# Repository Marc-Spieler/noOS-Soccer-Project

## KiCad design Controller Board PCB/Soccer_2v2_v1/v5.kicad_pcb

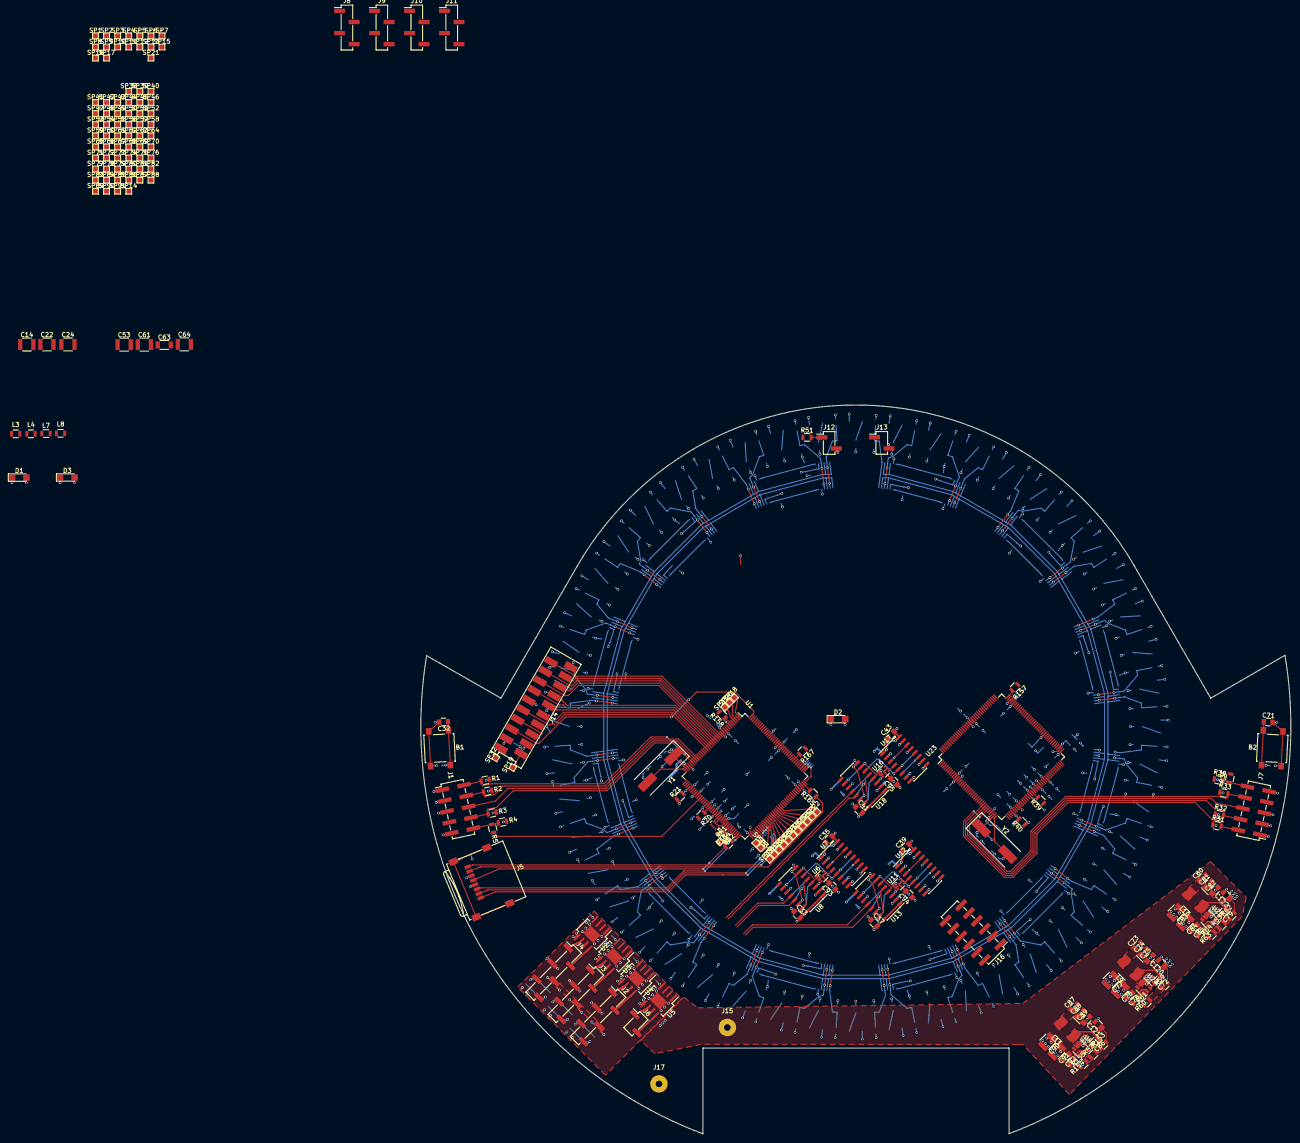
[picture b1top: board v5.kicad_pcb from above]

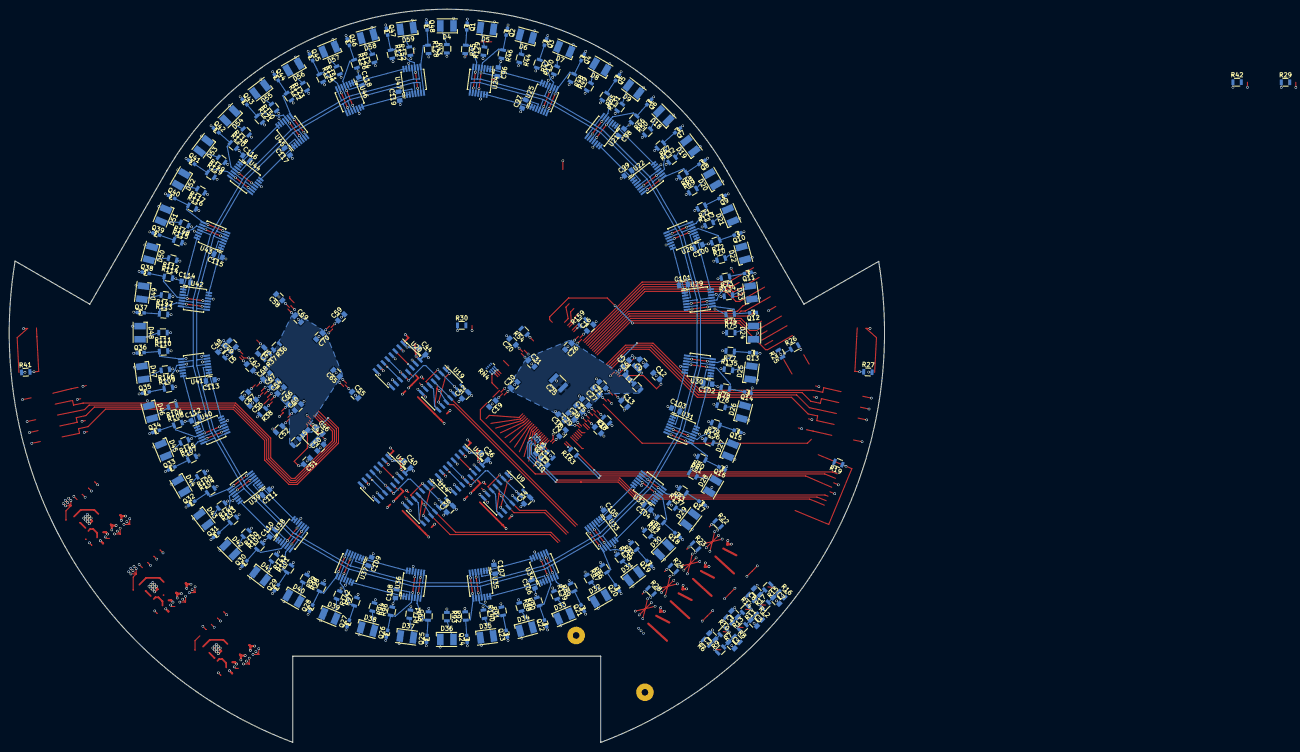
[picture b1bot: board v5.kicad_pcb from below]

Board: 4 copper layers, 199.2 x 166.8 mm, 554 parts (339 on the bottom side), 422 nets.

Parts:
B1, B2: BUTTON; SW_SPST_B3S-1000
C1, C2, C3, C4, C7, C8: opt.; C_0805
C5, C10, C11, C15, C16, C17, C18, C19, C20, C21, C23, C26, C27, C28, C29, C30, C31, C33, C34, C35, C36, C37, C38, C39, C40, C41, C42, C43, C44, C46, C48, C49, C54, C55, C56, C57, C58, C59, C60, C62, C65, C66, C67, C68, C69, C70, C72, C78, C79, C85, C86, C92, C93, C94, C95, C96, C97, C98, C99, C100, C101, C102, C103, C104, C105, C106, C107, C108, C109, C110, C111, C112, C113, C114, C115, C116, C117, C118, C119: 100n; C_0805
C6, C14, C22, C24, C25, C47, C53, C61, C64, C76, C77, C83, C84, C90, C91: 10u; C_1210
C9, C12, C13, C50, C51, C52: 22p; C_0805
C32, C71: 1u; C_0805
C45: 10n; C_0805
C63: 10u; C_1206
C73, C74, C75, C80, C81, C82, C87, C88, C89, C120, C121, C122: 22u; C_0805
D1: POW B; LED_1206
D2: LED O; LED_1206
D3: LED G; LED_1206
D4, D5, D6, D7, D8, D9, D18, D19, D20, D21, D22, D23, D24, D25, D26, D27, D28, D29, D30, D31, D32, D33, D34, D35, D36, D37, D38, D39, D40, D41, D42, D43, D44, D45, D46, D47, D48, D49, D50, D51, D52, D53, D54, D55, D56, D57, D58, D59: VLMW41R1T1; LED_PLCC-2
J1, J7: JTAG; Pin_Header_Straight_2x05_Pitch2.54mm_SMD
J2: Motor + Enc 1; Pin_Header_Straight_1x06_Pitch2.54mm_SMD_Pin1Left
J3: Motor + Enc 2; Pin_Header_Straight_1x06_Pitch2.54mm_SMD_Pin1Left
J4: Motor + Enc 3; Pin_Header_Straight_1x06_Pitch2.54mm_SMD_Pin1Left
J5: Micro_SD_Card; microSD_Card_Receptacle_Wuerth_693072010801
J6: Motor 4; Pin_Header_Straight_1x02_Pitch2.54mm_SMD_Pin1Left
J8: Ultrasonic 1; Pin_Header_Straight_1x04_Pitch2.54mm_SMD_Pin1Left
J9: Ultrasonic 2; Pin_Header_Straight_1x04_Pitch2.54mm_SMD_Pin1Left
J10: Ultrasonic 3; Pin_Header_Straight_1x04_Pitch2.54mm_SMD_Pin1Left
J11: Ultrasonic 4; Pin_Header_Straight_1x04_Pitch2.54mm_SMD_Pin1Left
J12: light_barrier transmitter; Pin_Header_Straight_1x02_Pitch2.54mm_SMD_Pin1Left
J13: light_barrier reciver; Pin_Header_Straight_1x02_Pitch2.54mm_SMD_Pin1Left
J14: UI+top; 2178711_Wire-To-Board_20-Pin_1,27mm_SMD
J15: POW_12V; SolderWirePad_single_1-5mmDrill
J16: Raspberry Pi; Pin_Header_Straight_2x06_Pitch2.54mm_SMD
J17: POW_GND; SolderWirePad_single_1-5mmDrill
L1, L2, L3, L4, L5, L6, L7, L8: 74279206; L_0805
L9, L10, L11: SRP5015TA-3R3M
Q1, Q2, Q3, Q4, Q5, Q6, Q7, Q8, Q9, Q10, Q11, Q12, Q13, Q14, Q15, Q16, Q17, Q18, Q19, Q20, Q21, Q22, Q23, Q24, Q25, Q26, Q27, Q28, Q29, Q30, Q31, Q32, Q33, Q34, Q35, Q36, Q37, Q38, Q39, Q40, Q41, Q42, Q43, Q44, Q45, Q46, Q47, Q48: KDT00030TR; ChipLED
R1, R2, R3, R4, R20, R31, R32, R33, R34, R37, R39: 100K; R_0805
R5, R18, R35, R38: 0; R_0805
R6, R8, R10, R12, R14, R16: 3.3K; R_0805
R7, R9, R11, R13, R15, R17: 2.2K; R_0805
R19: opt.; R_0805
R21, R40: 6.8K; R_0805
R22, R23, R24, R28: 27K; R_0805
R25, R26: 1.8K; R_0805
R27, R30, R41, R42: 68; R_0805
R29: 82; R_0805
R36: 330K; R_0805
R43, R44, R49, R50, R51, R69, R70, R75, R76, R81, R82, R87, R88, R93, R94, R99, R100, R105, R106, R111, R112, R117, R118, R123, R124, R129, R130, R131, R132, R133, R134, R135, R136, R137, R138, R139, R140, R141, R142, R143, R144, R145, R146, R147, R148, R149, R150, R151, R152: 160; R_0805
R45, R46, R47, R48, R65, R66, R67, R68, R71, R72, R73, R74, R77, R78, R79, R80, R83, R84, R85, R86, R89, R90, R91, R92, R95, R96, R97, R98, R101, R102, R103, R104, R107, R108, R109, R110, R113, R114, R115, R116, R119, R120, R121, R122, R125, R126, R127, R128: 6.2K; R_0805
R52, R53: 3.9K; R_0805
R54, R157, R158, R159, R163, R164, R165, R167: 22; R_0805
R59: 33.2K; R_0805
R60, R61, R63, R64, R154, R155: 10K; R_0805
R62, R153: 49.9K; R_0805
RN1, RN2, RN3, RN4: 4x22; R_Array_Concave_4x0402
SP1, SP2, SP3, SP4, SP5, SP6, SP7, SP8, SP9, SP10, SP11, SP12, SP13, SP14, SP15, SP16, SP17, SP18, SP19, SP20, SP21, SP22, SP23, SP24, SP25, SP26, SP27, SP28, SP29, SP30, SP31, SP32, SP33, SP34, SP35, SP36, SP37, SP38, SP39, SP40, SP41, SP42, SP43, SP44, SP45, SP46, SP47, SP48, SP49, SP50, SP51, SP52, SP53, SP54, SP55, SP56, SP57, SP58, SP59, SP60, SP61, SP62, SP63, SP64, SP65, SP66, SP67, SP68, SP69, SP70, SP71, SP72, SP73, SP74, SP75, SP76, SP77, SP78, SP79, SP80, SP81, SP82, SP83, SP84, SP85, SP86, SP87, SP88, SP89, SP90, SP91: solder_pad; WirePad_SMD 1,27x1,27mm
U1, U23: SAM3X8E; LQFP-144_20x20mm_Pitch0.5mm
U2, U3, U4, U5: DRV8871; HSOP_8-Pin_+_PowerPad
U6, U11, U16: 74HC2G04; SOT-363_SC-70-6
U7, U10, U12, U15, U17, U20: CD74HC191; SOIC-16_3.9x9.9mm_Pitch1.27mm
U8, U13, U18: CD74HC175; SOIC-16_3.9x9.9mm_Pitch1.27mm
U9, U14, U19: CD74HC86; SOIC-14_3.9x8.7mm_Pitch1.27mm
U21, U22, U24, U25, U26, U29, U30, U31, U32, U33, U34, U35, U36, U37, U38, U39, U40, U41, U42, U43, U44, U45, U46, U47: TLV1704; TSSOP-14_4.4x5mm_Pitch0.65mm
U27, U28, U48: TPS563209; SOT-23-6
Y1, Y2: FOXSDLF/120-20; Crystal_SMD_HC49-SD

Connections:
+3V3: C10.1, C14.1, C15.1, C16.1, C17.1, C18.1, C19.1, C20.1, C33.2, C34.2, C35.2, C36.2, C37.2, C38.2, C39.2, C40.2, C41.2, C42.2, C43.2, C44.2, C48.1, C53.1, C54.1, C55.1, C56.1, C57.1, C58.1, C59.1, C73.1, C74.1, C75.1, C93.2, C94.2, C95.2, C120.1, J1.1, J5.4, J7.1, L2.2, L3.1, L4.1, L6.1, L7.1, L8.1, L9.2, R1.1, R2.1, R3.1, R4.1, R20.2, R27.2, R31.1, R32.1, R33.1, R34.1, R39.2, R41.1, R59.2, U1.11, U1.52, U1.57, U1.62, U1.105, U1.125, U6.5, U7.16, U8.1, U8.16, U9.14, U10.16, U11.5, U12.16, U13.1, U13.16, U14.14, U15.16, U16.5, U17.16, U18.1, U18.16, U19.14, U20.16, U23.11, U23.52, U23.57, U23.62, U23.105, U23.125
+5V: C80.1, C81.1, C82.1, C96.2, C97.2, C98.2, C99.2, C100.2, C101.2, C102.2, C103.2, C104.2, C105.2, C106.2, C107.2, C108.2, C109.2, C110.2, C111.2, C112.2, C113.2, C114.2, C115.2, C116.2, C117.2, C118.2, C119.2, C122.1, L10.2, Q1.1, Q2.1, Q3.1, Q4.1, Q5.1, Q6.1, Q7.1, Q8.1, Q9.1, Q10.1, Q11.1, Q12.1, Q13.1, Q14.1, Q15.1, Q16.1, Q17.1, Q18.1, Q19.1, Q20.1, Q21.1, Q22.1, Q23.1, Q24.1, Q25.1, Q26.1, Q27.1, Q28.1, Q29.1, Q30.1, Q31.1, Q32.1, Q33.1, Q34.1, Q35.1, Q36.1, Q37.1, Q38.1, Q39.1, Q40.1, Q41.1, Q42.1, Q43.1, Q44.1, Q45.1, Q46.1, Q47.1, Q48.1, R43.1, R44.1, R49.1, R50.1, R62.2, R69.1, R70.1, R75.1, R76.1, R81.1, R82.1, R87.1, R88.1, R93.1, R94.1, R99.1, R100.1, R105.1, R106.1, R111.1, R112.1, R117.1, R118.1, R123.1, R124.1, R129.1, R130.1, R131.1, R132.1, R133.1, R134.1, R135.1, R136.1, R137.1, R138.1, R139.1, R140.1, R141.1, R142.1, R143.1, R144.1, R145.1, R146.1, R147.1, R148.1, R149.1, R150.1, R151.1, R152.1, U21.3, U22.3, U24.3, U25.3, U26.3, U29.3, U30.3, U31.3, U32.3, U33.3, U34.3, U35.3, U36.3, U37.3, U38.3, U39.3, U40.3, U41.3, U42.3, U43.3, U44.3, U45.3, U46.3, U47.3
+5VD: C87.1, C88.1, C89.1, C121.1, J2.4, J3.4, J4.4, J8.1, J9.1, J10.1, J11.1, J14.1, J16.4, L11.2, R25.1, R26.1, R29.2, R51.1, R153.2
+12V: C76.1, C77.1, C78.1, C83.1, C84.1, C85.1, C90.1, C91.1, C92.1, J15.1, R36.1, R60.2, R63.2, R154.2, U2.5, U3.5, U4.5, U5.5, U27.3, U28.3, U48.3
/BAT_LED: J14.8, U1.19
/Button_back: J14.7, U1.18
/Button_bot: J14.6, U1.17
/Button_left: J14.3, U1.14
/Button_mid: J14.4, U1.15
/Button_right: J14.5, U1.16
/Button_top: J14.2, U1.13
/CMPS03_PWM: J14.16, U1.144
/I²C_clock: J14.18, R26.2, U1.70
/I²C_data: J14.17, R25.2, U1.9
/M_LED1: J14.9, U1.20
/M_LED2: J14.11, U1.21
/M_LED3: J14.12, U1.22
/Motor Controller/ENC1A: U1.55, U7.3
/Motor Controller/ENC1B: U1.117, U7.2
/Motor Controller/ENC1C: U1.93, U7.6
/Motor Controller/ENC1D: U1.94, U7.7
/Motor Controller/ENC1E: U1.95, U10.3
/Motor Controller/ENC1F: U1.96, U10.2
/Motor Controller/ENC1G: U1.97, U10.6
/Motor Controller/ENC2A: U1.98, U12.3
/Motor Controller/ENC2B: U1.99, U12.2
/Motor Controller/ENC2C: U1.100, U12.6
/Motor Controller/ENC2D: U1.101, U12.7
/Motor Controller/ENC2E: U1.131, U15.3
/Motor Controller/ENC2F: U1.133, U15.2
/Motor Controller/ENC2G: U1.134, U15.6
/Motor Controller/ENC3A: U1.135, U17.3
/Motor Controller/ENC3B: U1.136, U17.2
/Motor Controller/ENC3C: U1.137, U17.6
/Motor Controller/ENC3D: U1.138, U17.7
/Motor Controller/ENC3E: U1.139, U20.3
/Motor Controller/ENC3F: U1.102, U20.2
/Motor Controller/ENC3G: U1.103, U20.6
/Motor Controller/ENC_CLK: R54.2, U7.14, U8.9, U10.14, U12.14, U13.9, U15.14, U17.14, U18.9, U20.14
/Motor Controller/ENC_LOAD: U1.113, U7.11, U10.11, U12.11, U15.11, U17.11, U20.11
/Motor Controller/Encoder 1/0: U8.2, U9.12
/Motor Controller/Encoder 1/1: U8.7, U9.1, U9.9
/Motor Controller/Encoder 1/2: U8.4, U8.10, U9.2, U9.13
/Motor Controller/Encoder 1/3: U8.5, U8.15, U9.10
/Motor Controller/Encoder 1/4: U9.4, U9.11
/Motor Controller/Encoder 1/5: U9.5, U9.8
/Motor Controller/Encoder 1/Direction: U7.5, U9.3, U10.5
/Motor Controller/Encoder 1/ENC1_out_A: C2.1, R6.1, R7.2, U8.13
/Motor Controller/Encoder 1/ENC1_out_B: C1.1, R8.1, R9.2, U8.12
/Motor Controller/Encoder 2/0: U13.2, U14.12
/Motor Controller/Encoder 2/1: U13.7, U14.1, U14.9
/Motor Controller/Encoder 2/2: U13.4, U13.10, U14.2, U14.13
/Motor Controller/Encoder 2/3: U13.5, U13.15, U14.10
/Motor Controller/Encoder 2/4: U14.4, U14.11
/Motor Controller/Encoder 2/5: U14.5, U14.8
/Motor Controller/Encoder 2/Direction: U12.5, U14.3, U15.5
/Motor Controller/Encoder 2/ENC2_out_A: C4.1, R10.1, R11.2, U13.13
/Motor Controller/Encoder 2/ENC2_out_B: C3.1, R12.1, R13.2, U13.12
/Motor Controller/Encoder 3/0: U18.2, U19.12
/Motor Controller/Encoder 3/1: U18.7, U19.1, U19.9
/Motor Controller/Encoder 3/2: U18.4, U18.10, U19.2, U19.13
/Motor Controller/Encoder 3/3: U18.5, U18.15, U19.10
/Motor Controller/Encoder 3/4: U19.4, U19.11
/Motor Controller/Encoder 3/5: U19.5, U19.8
/Motor Controller/Encoder 3/Direction: U17.5, U19.3, U20.5
/Motor Controller/Encoder 3/ENC3_out_A: C8.1, R14.1, R15.2, U18.13
/Motor Controller/Encoder 3/ENC3_out_B: C7.1, R16.1, R17.2, U18.12
/Motor Controller/JTAG_Test_Clock: J1.4, R2.2, U1.28
/Motor Controller/JTAG_Test_Data_In: J1.8, R3.2, U1.30
/Motor Controller/JTAG_Test_Data_Out: J1.6, U1.29
/Motor Controller/JTAG_Test_Mode_Select: J1.2, R1.2, U1.31
/Motor Controller/LED1: R30.2, U1.32
/Motor Controller/PWM0H: RN1.3, U1.60
/Motor Controller/PWM0L: RN1.4, U1.59
/Motor Controller/PWM1H: RN1.1, U1.63
/Motor Controller/PWM1L: R167.2, U1.116
/Motor Controller/PWM2H: RN2.3, U1.65
/Motor Controller/PWM2L: RN2.4, U1.64
/Motor Controller/PWM3H: RN2.1, U1.67
/Motor Controller/PWM3L: RN2.2, U1.66
/Motor Controller/RESET: B1.1, C32.1, R5.2, R27.1, U1.47
/Motor Controller/VDDANA: C23.1, C24.1, L3.2, U1.73
/Motor Controller/VDDOUT: C25.1, C26.1, C27.1, C28.1, C29.1, C30.1, C31.1, L1.2, U1.10, U1.45, U1.56, U1.61, U1.104, U1.124
/Motor Controller/VDDUTMI: C21.1, C22.1, L4.2, U1.41
/RPi1: J16.1, U1.23
/RPi2: J16.2, U1.24
/RPi3: J16.5, U1.25
/RPi4: J16.6, U1.26
/RPi5: J16.10, U1.27
/RPi6: J16.3, U1.2
/SPI0_CLK: J16.11, RN4.6
/SPI0_MISO: J16.9, RN4.8
/SPI0_MOSI: J16.7, RN4.7
/SPI0_SS0: J16.12, RN4.5
/SPI1_CLK: RN3.8, U23.110
/SPI1_MISO: R157.2, U23.108
/SPI1_MOSI: R158.2, U23.109
/SPI1_SS0: R159.2, U23.111
/Sensor Controller/1BLACK: U23.55, U24.1, U24.2, U25.13, U25.14
/Sensor Controller/1WHITE: U23.60, U24.13, U24.14, U25.1, U25.2
/Sensor Controller/2BLACK: U21.1, U21.2, U22.13, U22.14, U23.63
/Sensor Controller/2WHITE: U21.13, U21.14, U22.1, U22.2, U23.65
/Sensor Controller/3BLACK: U23.67, U26.1, U26.2, U29.13, U29.14
/Sensor Controller/3WHITE: U23.117, U26.13, U26.14, U29.1, U29.2
/Sensor Controller/4BLACK: U23.93, U30.1, U30.2, U31.13, U31.14
/Sensor Controller/4WHITE: U23.94, U30.13, U30.14, U31.1, U31.2
/Sensor Controller/5BLACK: U23.95, U32.1, U32.2, U33.13, U33.14
/Sensor Controller/5WHITE: U23.96, U32.13, U32.14, U33.1, U33.2
/Sensor Controller/6BLACK: U23.97, U34.1, U34.2, U35.13, U35.14
/Sensor Controller/6WHITE: U23.98, U34.13, U34.14, U35.1, U35.2
/Sensor Controller/7BLACK: U23.99, U36.1, U36.2, U37.13, U37.14
/Sensor Controller/7WHITE: U23.100, U36.13, U36.14, U37.1, U37.2
/Sensor Controller/8BLACK: U23.101, U38.1, U38.2, U39.13, U39.14
/Sensor Controller/8WHITE: U23.131, U38.13, U38.14, U39.1, U39.2
/Sensor Controller/9BLACK: U23.132, U40.1, U40.2, U41.13, U41.14
/Sensor Controller/9WHITE: U23.133, U40.13, U40.14, U41.1, U41.2
/Sensor Controller/10BLACK: U23.134, U42.1, U42.2, U43.13, U43.14
/Sensor Controller/10WHITE: U23.135, U42.13, U42.14, U43.1, U43.2
/Sensor Controller/11BLACK: U23.137, U44.1, U44.2, U45.13, U45.14
/Sensor Controller/11WHITE: U23.138, U44.13, U44.14, U45.1, U45.2
/Sensor Controller/12BLACK: U23.102, U46.1, U46.2, U47.13, U47.14
/Sensor Controller/12WHITE: U23.103, U46.13, U46.14, U47.1, U47.2
/Sensor Controller/Echo1: J8.3, U23.85
/Sensor Controller/Echo2: J9.3, U23.25
/Sensor Controller/Echo3: J10.3, U23.136
/Sensor Controller/Echo4: J11.3, U23.139
/Sensor Controller/JTAG_Test_Clock: J7.4, R32.2, U23.28
/Sensor Controller/JTAG_Test_Data_In: J7.8, R33.2, U23.30
/Sensor Controller/JTAG_Test_Data_Out: J7.6, U23.29
/Sensor Controller/JTAG_Test_Mode_Select: J7.2, R31.2, U23.31
/Sensor Controller/LBR: J13.1, U23.83
/Sensor Controller/LED2: R42.2, U23.16
/Sensor Controller/Linesensor 1/Photo1: Q1.2, R45.1, U24.6, U24.9
/Sensor Controller/Linesensor 1/Photo2: Q2.2, R46.1, U24.4, U24.11
/Sensor Controller/Linesensor 1/Photo3: Q3.2, R47.1, U25.5, U25.10
/Sensor Controller/Linesensor 1/Photo4: Q4.2, R48.1, U25.7, U25.8
/Sensor Controller/Linesensor 2/Photo1: Q5.2, R65.1, U21.6, U21.9
/Sensor Controller/Linesensor 2/Photo2: Q6.2, R66.1, U21.4, U21.11
/Sensor Controller/Linesensor 2/Photo3: Q7.2, R67.1, U22.5, U22.10
/Sensor Controller/Linesensor 2/Photo4: Q8.2, R68.1, U22.7, U22.8
/Sensor Controller/Linesensor 3/Photo1: Q9.2, R71.1, U26.6, U26.9
/Sensor Controller/Linesensor 3/Photo2: Q10.2, R72.1, U26.4, U26.11
/Sensor Controller/Linesensor 3/Photo3: Q11.2, R73.1, U29.5, U29.10
/Sensor Controller/Linesensor 3/Photo4: Q12.2, R74.1, U29.7, U29.8
/Sensor Controller/Linesensor 4/Photo1: Q13.2, R77.1, U30.6, U30.9
/Sensor Controller/Linesensor 4/Photo2: Q14.2, R78.1, U30.4, U30.11
/Sensor Controller/Linesensor 4/Photo3: Q15.2, R79.1, U31.5, U31.10
/Sensor Controller/Linesensor 4/Photo4: Q16.2, R80.1, U31.7, U31.8
/Sensor Controller/Linesensor 5/Photo1: Q17.2, R83.1, U32.6, U32.9
/Sensor Controller/Linesensor 5/Photo2: Q18.2, R84.1, U32.4, U32.11
/Sensor Controller/Linesensor 5/Photo3: Q19.2, R85.1, U33.5, U33.10
/Sensor Controller/Linesensor 5/Photo4: Q20.2, R86.1, U33.7, U33.8
/Sensor Controller/Linesensor 6/Photo1: Q21.2, R89.1, U34.6, U34.9
/Sensor Controller/Linesensor 6/Photo2: Q22.2, R90.1, U34.4, U34.11
/Sensor Controller/Linesensor 6/Photo3: Q23.2, R91.1, U35.5, U35.10
/Sensor Controller/Linesensor 6/Photo4: Q24.2, R92.1, U35.7, U35.8
/Sensor Controller/Linesensor 7/Photo1: Q25.2, R95.1, U36.6, U36.9
/Sensor Controller/Linesensor 7/Photo2: Q26.2, R96.1, U36.4, U36.11
/Sensor Controller/Linesensor 7/Photo3: Q27.2, R97.1, U37.5, U37.10
/Sensor Controller/Linesensor 7/Photo4: Q28.2, R98.1, U37.7, U37.8
/Sensor Controller/Linesensor 8/Photo1: Q29.2, R101.1, U38.6, U38.9
/Sensor Controller/Linesensor 8/Photo2: Q30.2, R102.1, U38.4, U38.11
/Sensor Controller/Linesensor 8/Photo3: Q31.2, R103.1, U39.5, U39.10
/Sensor Controller/Linesensor 8/Photo4: Q32.2, R104.1, U39.7, U39.8
/Sensor Controller/Linesensor 9/Photo1: Q33.2, R107.1, U40.6, U40.9
/Sensor Controller/Linesensor 9/Photo2: Q34.2, R108.1, U40.4, U40.11
/Sensor Controller/Linesensor 9/Photo3: Q35.2, R109.1, U41.5, U41.10
/Sensor Controller/Linesensor 9/Photo4: Q36.2, R110.1, U41.7, U41.8
/Sensor Controller/Linesensor 10/Photo1: Q37.2, R113.1, U42.6, U42.9
/Sensor Controller/Linesensor 10/Photo2: Q38.2, R114.1, U42.4, U42.11
/Sensor Controller/Linesensor 10/Photo3: Q39.2, R115.1, U43.5, U43.10
/Sensor Controller/Linesensor 10/Photo4: Q40.2, R116.1, U43.7, U43.8
/Sensor Controller/Linesensor 11/Photo1: Q41.2, R119.1, U44.6, U44.9
/Sensor Controller/Linesensor 11/Photo2: Q42.2, R120.1, U44.4, U44.11
/Sensor Controller/Linesensor 11/Photo3: Q43.2, R121.1, U45.5, U45.10
/Sensor Controller/Linesensor 11/Photo4: Q44.2, R122.1, U45.7, U45.8
/Sensor Controller/Linesensor 12/Photo1: Q45.2, R125.1, U46.6, U46.9
/Sensor Controller/Linesensor 12/Photo2: Q46.2, R126.1, U46.4, U46.11
/Sensor Controller/Linesensor 12/Photo3: Q47.2, R127.1, U47.5, U47.10
/Sensor Controller/Linesensor 12/Photo4: Q48.2, R128.1, U47.7, U47.8
/Sensor Controller/RESET: B2.1, C71.1, R35.2, R41.2, U23.47
/Sensor Controller/Trig1: J8.2, U23.59
/Sensor Controller/Trig2: J9.2, U23.116
/Sensor Controller/Trig3: J10.2, U23.64
/Sensor Controller/Trig4: J11.2, U23.66
/Sensor Controller/VDDANA: C62.1, C63.1, L7.2, U23.73
/Sensor Controller/VDDOUT: C64.1, C65.1, C66.1, C67.1, C68.1, C69.1, C70.1, L5.2, U23.10, U23.45, U23.56, U23.61, U23.104, U23.124
/Sensor Controller/VDDUTMI: C60.1, C61.1, L8.2, U23.41
/Sensor Controller/VREF_black: U21.5, U21.7, U22.9, U22.11, U23.76, U24.5, U24.7, U25.9, U25.11, U26.5, U26.7, U29.9, U29.11, U30.5, U30.7, U31.9, U31.11, U32.5, U32.7, U33.9, U33.11, U34.5, U34.7, U35.9, U35.11, U36.5, U36.7, U37.9, U37.11, U38.5, U38.7, U39.9, U39.11, U40.5, U40.7, U41.9, U41.11, U42.5, U42.7, U43.9, U43.11, U44.5, U44.7, U45.9, U45.11, U46.5, U46.7, U47.9, U47.11
/Sensor Controller/VREF_white: U21.8, U21.10, U22.4, U22.6, U23.77, U24.8, U24.10, U25.4, U25.6, U26.8, U26.10, U29.4, U29.6, U30.8, U30.10, U31.4, U31.6, U32.8, U32.10, U33.4, U33.6, U34.8, U34.10, U35.4, U35.6, U36.8, U36.10, U37.4, U37.6, U38.8, U38.10, U39.4, U39.6, U40.8, U40.10, U41.4, U41.6, U42.8, U42.10, U43.4, U43.6, U44.8, U44.10, U45.4, U45.6, U46.8, U46.10, U47.4, U47.6
GND: B1.2, B2.2, C1.2, C2.2, C3.2, C4.2, C5.2, C6.2, C7.2, C8.2, C9.1, C10.2, C11.2, C12.1, C13.2, C14.2, C15.2, C16.2, C17.2, C18.2, C19.2, C20.2, C21.2, C22.2, C23.2, C24.2, C25.2, C26.2, C27.2, C28.2, C29.2, C30.2, C31.2, C32.2, C33.1, C34.1, C35.1, C36.1, C37.1, C38.1, C39.1, C40.1, C41.1, C42.1, C43.1, C44.1, C45.2, C46.2, C47.2, C48.2, C49.2, C50.1, C51.1, C52.2, C53.2, C54.2, C55.2, C56.2, C57.2, C58.2, C59.2, C60.2, C61.2, C62.2, C63.2, C64.2, C65.2, C66.2, C67.2, C68.2, C69.2, C70.2, C71.2, C73.2, C74.2, C75.2, C76.2, C77.2, C78.2, C80.2, C81.2, C82.2, C83.2, C84.2, C85.2, C87.2, C88.2, C89.2, C90.2, C91.2, C92.2, C93.1, C94.1, C95.1, C96.1, C97.1, C98.1, C99.1, C100.1, C101.1, C102.1, C103.1, C104.1, C105.1, C106.1, C107.1, C108.1, C109.1, C110.1, C111.1, C112.1, C113.1, C114.1, C115.1, C116.1, C117.1, C118.1, C119.1, C120.2, C121.2, C122.2, D1.1, D2.1, D3.1, D4.1, D5.1, D6.1, D7.1, D8.1, D9.1, D18.1, D19.1, D20.1, D21.1, D22.1, D23.1, D24.1, D25.1, D26.1, D27.1, D28.1, D29.1, D30.1, D31.1, D32.1, D33.1, D34.1, D35.1, D36.1, D37.1, D38.1, D39.1, D40.1, D41.1, D42.1, D43.1, D44.1, D45.1, D46.1, D47.1, D48.1, D49.1, D50.1, D51.1, D52.1, D53.1, D54.1, D55.1, D56.1, D57.1, D58.1, D59.1, J1.3, J1.5, J1.9, J2.3, J3.3, J4.3, J5.6, J7.3, J7.5, J7.9, J8.4, J9.4, J10.4, J11.4, J12.2, J13.2, J14.10, J16.8, J17.1, R6.2, R8.2, R10.2, R12.2, R14.2, R16.2, R18.2, R19.2, R21.2, R22.2, R23.2, R24.2, R28.2, R37.2, R38.2, R40.2, R45.2, R46.2, R47.2, R48.2, R61.1, R64.1, R65.2, R66.2, R67.2, R68.2, R71.2, R72.2, R73.2, R74.2, R77.2, R78.2, R79.2, R80.2, R83.2, R84.2, R85.2, R86.2, R89.2, R90.2, R91.2, R92.2, R95.2, R96.2, R97.2, R98.2, R101.2, R102.2, R103.2, R104.2, R107.2, R108.2, R109.2, R110.2, R113.2, R114.2, R115.2, R116.2, R119.2, R120.2, R121.2, R122.2, R125.2, R126.2, R127.2, R128.2, R155.1, U1.12, U1.33, U1.44, U1.54, U1.58, U1.74, U1.106, U1.126, U2.1, U2.7, U3.1, U3.7, U4.1, U4.7, U5.1, U5.7, U6.1, U6.2, U7.1, U7.8, U7.9, U7.10, U7.15, U8.8, U9.7, U10.1, U10.8, U10.9, U10.10, U10.15, U11.1, U11.2, U12.1, U12.8, U12.9, U12.10, U12.15, U13.8, U14.7, U15.1, U15.8, U15.9, U15.10, U15.15, U16.1, U16.2, U17.1, U17.8, U17.9, U17.10, U17.15, U18.8, U19.7, U20.1, U20.8, U20.9, U20.10, U20.15, U21.12, U22.12, U23.12, U23.33, U23.44, U23.54, U23.58, U23.74, U23.106, U23.126, U24.12, U25.12, U26.12, U27.1, U28.1, U29.12, U30.12, U31.12, U32.12, U33.12, U34.12, U35.12, U36.12, U37.12, U38.12, U39.12, U40.12, U41.12, U42.12, U43.12, U44.12, U45.12, U46.12, U47.12, U48.1
unnamed: C5.1, C6.1, L1.1, U1.34
unnamed: C9.2, U1.35, Y1.1
unnamed: C11.1, L2.1, U1.75
unnamed: C12.2, U1.36, Y1.2
unnamed: C13.1, R21.1, U1.40
unnamed: C45.1, R36.2, R37.1, U23.84
unnamed: C46.1, C47.1, L5.1, U23.34
unnamed: C49.1, L6.2, U23.75
unnamed: C50.2, U23.35, Y2.1
unnamed: C51.2, U23.36, Y2.2
unnamed: C52.1, R40.1, U23.40
unnamed: C72.1, L9.1, U27.2
unnamed: C72.2, U27.6
unnamed: C79.1, L10.1, U28.2
unnamed: C79.2, U28.6
unnamed: C86.1, L11.1, U48.2
unnamed: C86.2, U48.6
unnamed: D1.2, R29.1
unnamed: D2.2, R30.1
unnamed: D3.2, R42.1
unnamed: D4.2, R43.2
unnamed: D5.2, R129.2
unnamed: D6.2, R44.2
unnamed: D7.2, R130.2
unnamed: D8.2, R49.2
unnamed: D9.2, R131.2
unnamed: D18.2, R50.2
unnamed: D19.2, R132.2
unnamed: D20.2, R69.2
unnamed: D21.2, R133.2
unnamed: D22.2, R70.2
unnamed: D23.2, R134.2
unnamed: D24.2, R75.2
unnamed: D25.2, R135.2
unnamed: D26.2, R76.2
unnamed: D27.2, R136.2
unnamed: D28.2, R81.2
unnamed: D29.2, R137.2
unnamed: D30.2, R82.2
unnamed: D31.2, R138.2
unnamed: D32.2, R87.2
unnamed: D33.2, R139.2
unnamed: D34.2, R88.2
unnamed: D35.2, R140.2
unnamed: D36.2, R93.2
unnamed: D37.2, R141.2
unnamed: D38.2, R94.2
unnamed: D39.2, R142.2
unnamed: D40.2, R99.2
unnamed: D41.2, R143.2
unnamed: D42.2, R100.2
unnamed: D43.2, R144.2
unnamed: D44.2, R105.2
unnamed: D45.2, R145.2
unnamed: D46.2, R106.2
unnamed: D47.2, R146.2
unnamed: D48.2, R111.2
unnamed: D49.2, R147.2
unnamed: D50.2, R112.2
unnamed: D51.2, R148.2
unnamed: D52.2, R117.2
unnamed: D53.2, R149.2
unnamed: D54.2, R118.2
unnamed: D55.2, R150.2
unnamed: D56.2, R123.2
unnamed: D57.2, R151.2
unnamed: D58.2, R124.2
unnamed: D59.2, R152.2
unnamed: J1.10, R4.2, R5.1
unnamed: J2.1, U4.6
unnamed: J2.2, U4.8
unnamed: J2.5, R7.1
unnamed: J2.6, R9.1
unnamed: J3.1, U3.6
unnamed: J3.2, U3.8
unnamed: J3.5, R11.1
unnamed: J3.6, R13.1
unnamed: J4.1, U2.6
unnamed: J4.2, U2.8
unnamed: J4.5, R15.1
unnamed: J4.6, R17.1
unnamed: J5.1, RN3.6
unnamed: J5.2, RN3.7
unnamed: J5.3, R163.1
unnamed: J5.5, R164.1
unnamed: J5.7, R165.1
unnamed: J5.8, RN3.5
unnamed: J5.9, R19.1
unnamed: J6.1, U5.6
unnamed: J6.2, U5.8
unnamed: J7.10, R34.2, R35.1
unnamed: J12.1, R51.2
unnamed: J14.19, SP19.1
unnamed: J14.20, SP32.1
unnamed: R18.1, U1.51
unnamed: R20.1, U1.53
unnamed: R22.1, U2.4
unnamed: R23.1, U3.4
unnamed: R24.1, U4.4
unnamed: R28.1, U5.4
unnamed: R38.1, U23.51
unnamed: R39.1, U23.53
unnamed: R53.1, R64.2, U28.4
unnamed: R53.2, R62.1
unnamed: R54.1, U1.132
unnamed: R59.1, R61.2, U27.4
unnamed: R60.1, U27.5
unnamed: R63.1, U28.5
unnamed: R52.2, R153.1
unnamed: R154.1, U48.5
unnamed: R52.1, R155.2, U48.4
unnamed: R157.1, U1.5
unnamed: R158.1, U1.6
unnamed: R159.1, U1.7
unnamed: R163.2, U1.72
unnamed: R164.2, U1.71
unnamed: R165.2, U1.107
unnamed: R167.1, U3.3
unnamed: RN1.5, U2.3
unnamed: RN1.6, U2.2
unnamed: RN1.8, U3.2
unnamed: RN2.5, U4.3
unnamed: RN2.6, U4.2
unnamed: RN2.7, U5.3
unnamed: RN2.8, U5.2
unnamed: RN3.1, U1.78
unnamed: RN3.2, U1.79
unnamed: RN3.3, U1.80
unnamed: RN3.4, U1.81
unnamed: RN4.1, U1.108
unnamed: RN4.2, U1.109
unnamed: RN4.3, U1.110
unnamed: RN4.4, U1.111
unnamed: SP1.1, U1.143
unnamed: SP2.1, U1.142
unnamed: SP3.1, U1.141
unnamed: SP4.1, U1.140
unnamed: SP5.1, U23.144
unnamed: SP6.1, U1.129
unnamed: SP7.1, U1.128
unnamed: SP8.1, U1.127
unnamed: SP9.1, U1.123
unnamed: SP10.1, U1.122
unnamed: SP11.1, U1.121
unnamed: SP12.1, U1.120
unnamed: SP13.1, U1.119
unnamed: SP14.1, U1.118
unnamed: SP15.1, U1.115
unnamed: SP16.1, U1.114
unnamed: SP17.1, U1.112
unnamed: SP18.1, U1.1
unnamed: SP20.1, U1.3
unnamed: SP21.1, U1.8
unnamed: SP22.1, U1.92
unnamed: SP23.1, U1.91
unnamed: SP24.1, U1.90
unnamed: SP25.1, U1.89
unnamed: SP26.1, U1.88
unnamed: SP27.1, U1.87
unnamed: SP28.1, U1.86
unnamed: SP29.1, U1.85
unnamed: SP30.1, U1.84
unnamed: SP31.1, U1.83
unnamed: SP33.1, U1.82
unnamed: SP34.1, U1.77
unnamed: SP35.1, U1.76
unnamed: SP36.1, U1.68
unnamed: SP37.1, U1.4
unnamed: SP38.1, U23.143
unnamed: SP39.1, U23.142
unnamed: SP40.1, U23.141
unnamed: SP41.1, U23.140
unnamed: SP42.1, U23.129
unnamed: SP43.1, U23.128
unnamed: SP44.1, U23.127
unnamed: SP45.1, U23.123
unnamed: SP46.1, U23.122
unnamed: SP47.1, U23.121
unnamed: SP48.1, U23.120
unnamed: SP49.1, U23.119
unnamed: SP50.1, U23.118
unnamed: SP51.1, U23.115
unnamed: SP52.1, U23.114
unnamed: SP53.1, U23.113
unnamed: SP54.1, U23.112
unnamed: SP55.1, U23.1
unnamed: SP56.1, U23.2
unnamed: SP57.1, U23.107
unnamed: SP58.1, U23.3
unnamed: SP59.1, U23.4
unnamed: SP60.1, U23.5
unnamed: SP61.1, U23.6
unnamed: SP62.1, U23.7
unnamed: SP63.1, U23.8
unnamed: SP64.1, U23.9
unnamed: SP65.1, U23.17
unnamed: SP66.1, U23.92
unnamed: SP67.1, U23.18
unnamed: SP68.1, U23.91
unnamed: SP69.1, U23.19
unnamed: SP70.1, U23.90
unnamed: SP71.1, U23.20
unnamed: SP72.1, U23.89
unnamed: SP73.1, U23.21
unnamed: SP74.1, U23.88
unnamed: SP75.1, U23.22
unnamed: SP76.1, U23.87
unnamed: SP77.1, U23.23
unnamed: SP78.1, U23.86
unnamed: SP79.1, U23.24
unnamed: SP80.1, U23.26
unnamed: SP81.1, U23.27
unnamed: SP82.1, U23.82
unnamed: SP83.1, U23.81
unnamed: SP84.1, U23.80
unnamed: SP85.1, U23.79
unnamed: SP86.1, U23.78
unnamed: SP87.1, U23.32
unnamed: SP88.1, U23.68
unnamed: SP89.1, U23.70
unnamed: SP90.1, U23.71
unnamed: SP91.1, U23.72
unnamed: U6.3, U9.6
unnamed: U6.4, U7.4
unnamed: U7.13, U10.4
unnamed: U11.3, U14.6
unnamed: U11.4, U12.4
unnamed: U12.13, U15.4
unnamed: U16.3, U19.6
unnamed: U16.4, U17.4
unnamed: U17.13, U20.4

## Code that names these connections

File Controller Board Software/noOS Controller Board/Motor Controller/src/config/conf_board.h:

/************************************************************************/
/* Author: Marc Spieler                                                 */
/* Team: NoOS                                                           */
/* Created: 01.07.2018                                                  */
/************************************************************************/

#ifndef CONF_BOARD_H
#define CONF_BOARD_H

/* Board oscillator settings */
#define BOARD_FREQ_SLCK_XTAL                    (32768U)
#define BOARD_FREQ_SLCK_BYPASS                  (32768U)
#define BOARD_FREQ_MAINCK_XTAL                  (12000000U)
#define BOARD_FREQ_MAINCK_BYPASS                (12000000U)

/* Master clock frequency */
#define BOARD_MCK                               (CHIP_FREQ_CPU_MAX)
#define BOARD_NO_32K_XTAL

/* board main clock xtal startup time */
#define BOARD_OSC_STARTUP_US                    (15625)

/* Family definition (already defined) */
#define sam3x

/* Core definition */
#define cortexm3

/* PWM settings */
#define PWM_FREQUENCY                           (20000)
#define PERIOD_VALUE                            (1000)
#define INIT_DUTY_VALUE                         (500)

/** Enable SD MMC interface pins through HSMCI */
#define CONF_BOARD_SD_MMC_HSMCI
#define SD_MMC_HSMCI_MEM_CNT                    (1)
#define SD_MMC_HSMCI_SLOT_0_SIZE                (4)

/* Signal LED pin definition */
#define LED_ONBOARD                             (PIO_PD10_IDX)
#define LED_M1                                  (PIO_PD7_IDX)
#define LED_M2                                  (PIO_PD8_IDX)
#define LED_M3                                  (PIO_PD9_IDX)
#define LED_BAT                                 (PIO_PD6_IDX)

/* Battery warner pin definition */
/*#define BAT_WARN                                (PWM_CHANNEL_3)
#define BAT_WARN_PIN                            (PIO_PC8_IDX)*/

/* Pushbutton pin definition */
#define PB_UP                                   (PIO_PD0_IDX)
#define PB_LEFT                                 (PIO_PD1_IDX)
#define PB_MID                                  (PIO_PD2_IDX)
#define PB_RIGHT                                (PIO_PD3_IDX)
#define PB_DOWN                                 (PIO_PD4_IDX)
#define PB_RETURN                               (PIO_PD5_IDX)

/* Raspberry Pi GPIO pin definition */
#define RPI1                                    (PIO_PA1_IDX)
//#define RPI2                                    (PIO_PA8_IDX)
//#define RPI3                                    (PIO_PA9_IDX)
#define RPI4                                    (PIO_PA7_IDX)
#define RPI5                                    (PIO_PA5_IDX)
#define RPI6                                    (PIO_PA0_IDX)

/* Kicker pin definition */
#define KICK_TRIG                               (PIO_PB24_IDX)
//#define KICK_VOLTAGE                            (PIO_PB21_IDX)
#define KICK_VOLTAGE                            (ADC_CHANNEL_14)


/* Motor pin definition */
#define MOTOR_LEFT           				    (PWM_CHANNEL_0)
#define MOTOR_LEFT_L					        (PIO_PC2_IDX)
#define MOTOR_LEFT_H				            (PIO_PC3_IDX)
#define MOTOR_RIGHT                             (PWM_CHANNEL_1)
#define MOTOR_RIGHT_L                           (PIO_PC4_IDX)
#define MOTOR_RIGHT_H                           (PIO_PC5_IDX)
#define MOTOR_REAR                              (PWM_CHANNEL_2)
#define MOTOR_REAR_L                            (PIO_PC6_IDX)
#define MOTOR_REAR_H                            (PIO_PC7_IDX)

/* Encoder pin definition */
#define ENC_CLK                                 (PWM_CHANNEL_4)
#define ENC_CLK_PIN                             (PIO_PC21_IDX)
#define ENC_LOAD                                (PIO_PB0_IDX)

#define ENC_LEFT_A						        (PIO_PC24_IDX)
#define ENC_LEFT_B						        (PIO_PC25_IDX)
#define ENC_LEFT_C						        (PIO_PC26_IDX)
#define ENC_LEFT_D						        (PIO_PC27_IDX)
#define ENC_LEFT_E						        (PIO_PC28_IDX)
#define ENC_LEFT_F						        (PIO_PC29_IDX)
#define ENC_LEFT_G						        (PIO_PC30_IDX)

#define ENC_RIGHT_A						        (PIO_PC16_IDX)
#define ENC_RIGHT_B						        (PIO_PC17_IDX)
#define ENC_RIGHT_C						        (PIO_PC18_IDX)
#define ENC_RIGHT_D                             (PIO_PC19_IDX)
#define ENC_RIGHT_E						        (PIO_PC20_IDX)
#define ENC_RIGHT_F						        (PIO_PC22_IDX)
#define ENC_RIGHT_G						        (PIO_PC23_IDX)

#define ENC_REAR_A						        (PIO_PC1_IDX)
#define ENC_REAR_B					            (PIO_PC10_IDX)
#define ENC_REAR_C						        (PIO_PC11_IDX)
#define ENC_REAR_D						        (PIO_PC12_IDX)
#define ENC_REAR_E						        (PIO_PC13_IDX)
#define ENC_REAR_F						        (PIO_PC14_IDX)
#define ENC_REAR_G						        (PIO_PC15_IDX)

/* UART pin definition */
#define UART_RX                                 (PIO_PA10_IDX)
#define UART_TX                                 (PIO_PA11_IDX)

/* I2C0 pin definition */
#define I2C0_DATA                               (PIO_PA17_IDX)
#define I2C0_CLK                                (PIO_PA18_IDX)

/* SPI1 pin definition */
#define SPI1_MISO                               (PIO_PA12_IDX)
#define SPI1_MOSI                               (PIO_PA13_IDX)
#define SPI1_SPCK                               (PIO_PA16_IDX)
#define SPI1_NPCS0                              (PIO_PA14_IDX)

/* micro SD Card pin definition */
#define MSD_CMD                                 (PIO_PA20_IDX)
#define MSD_CLK                                 (PIO_PA19_IDX)
#define MSD_DATA0                               (PIO_PA21_IDX)
#define MSD_DATA1                               (PIO_PA22_IDX)
#define MSD_DATA2                               (PIO_PA23_IDX)
#define MSD_DATA3                               (PIO_PA24_IDX)

#endif

#if 0

#ifndef CONF_BOARD_H_INCLUDED
#define CONF_BOARD_H_INCLUDED

/** Enable Com Port. */
#define CONF_BOARD_UART_CONSOLE

//! [tc_define_peripheral]
/* Use TC Peripheral 0. */
#define TC             TC0
#define TC_PERIPHERAL  0
//! [tc_define_peripheral]

//! [tc_define_ch1]
/* Configure TC0 channel 1 as waveform output. */
#define TC_CHANNEL_WAVEFORM 1
#define ID_TC_WAVEFORM      ID_TC1
#define PIN_TC_WAVEFORM     PIN_TC0_TIOA1
#define PIN_TC_WAVEFORM_MUX PIN_TC0_TIOA1_MUX
//! [tc_define_ch1]

//! [tc_define_ch2]
/* Configure TC0 channel 2 as capture input. */
#define TC_CHANNEL_CAPTURE 2
#define ID_TC_CAPTURE ID_TC2
#define PIN_TC_CAPTURE PIN_TC0_TIOA2
#define PIN_TC_CAPTURE_MUX PIN_TC0_TIOA2_MUX
//! [tc_define_ch2]

//! [tc_define_irq_handler]
/* Use TC2_Handler for TC capture interrupt. */
#define TC_Handler  TC2_Handler
#define TC_IRQn     TC2_IRQn
//! [tc_define_irq_handler]

#endif /* CONF_BOARD_H_INCLUDED */

#endif

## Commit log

2018-08-19 Initial Version
    Updated Folder Structure and created Contoller Board Project
2018-08-19 Added Raspberry Pi Software
    Added Raspberry Pi Software
2018-08-19 Added Documetation
    Added Documetation
2018-08-19 Added Contoller Board PCB
    Added Contoller Board PCB
2018-08-19 Changes to Controller Board PCB folder
    Changes to Controller Board PCB folder
2018-08-19 Controller Board Setup (not completed)
    Controller Board Setup (not completed)
2018-08-19 Controller Board Setup (not completed, but working)
    Controller Board Setup (not completed, but working)
2018-08-19 Controller Board Setup (not completed, not working)
    Controller Board Setup (not completed, not working)
2018-08-21 Controller Board Steup (not completed, not working)
    Controller Board Steup (not completed, not working)
2018-08-22 Raspberry Pi Software reformat
    Raspberry Pi Software reformat
2018-08-26 Controller Board Setup (not completed, but working)
    Controller Board Setup (not completed, but working)
    Implemented PDC for TWI communication
2018-09-01 Controllerr Board Setup (not completed, but working)
    Controllerr Board Setup (not completed, but working)
    Implemented function for 4-line LCD update and PDC for TWI
2018-11-10 Controller Board Setup (not completed, but working)
    Started the battery percentage display in main menu replacing the battery voltage display
2018-11-11 Controller Board Setup (not completed, but working)
    Battery percentage display completed
2019-03-01 Changes since last commit
2019-03-01 removed ultrasonic distance measurement from sensor controller
2019-03-09 added Controller Board PCB files
2019-03-09 implemented SD card test
2019-03-15 some changes
2019-03-25 wip
    implemented motors
    encoder not working
2019-03-25 removed unfinished progress
    removed unfinished progress to create seperate branches
2019-03-25 wip
    added basic motor, encoder and pid implementation
    encoder doesn't work yet
2019-03-30 completed motor and encoder setup
2019-03-30 added 3D Models
2019-03-30 Revert "added 3D Models"
    This reverts commit dd66d6f76c6984506f98c6ab55a91cd58704d50a.
2019-03-30 added 3D Models
    - Batteryholder
    - PCB protectors (left and right)
2019-03-30 Added 3D Models
    -modified folder structure
    -added Blender files:
    -cameraRaspberryexportCover.blend
    -cameraRaspberryexportMain.blend
    -added stl files:
    -cameraRaspberryexportCover.stl
2019-04-06 errorless build, not tested
2019-04-06 wip
    trouble with display issues
2019-04-07 implementation completed
    waiting to proof 30 Hz update rate
2019-04-12 wip
    updated data structure
2019-04-13 updated documentation
    added SPI communication protocol between Motor Controller and Raspberry Pi
2019-04-16 wip
    removed heartbeat delay in camera menu
2019-04-17 wip
    line detection and esc calculation working
2019-04-17 wip
    line calibration implemented (not tested)
2019-04-19 wip
    write time tests implemented (working)
2019-04-19 removed unneccesary files
2019-04-19 removed debug folder
2019-04-19 Revert "Merge branch 'sd-card-implementation' into Controller-Board-Setup"
    This reverts commit 3a77dfa97d5c83ed78d6e3cacdfeb91060f32596, reversing
    changes made to 0760e1c1ec8f6013e981f2bdd808d7c4e8a41008.
2019-04-19 Revert "wip"
    This reverts commit 2cf78360317c598949d830d77e44c19391013b92.
2019-04-19 manually merged SD-Card implementation
2019-04-20 wip
    included iniparser lib and battery warner
2019-04-20 wip
    line calibration over menu working
2019-04-22 removed battery warner
2019-04-24 manually merged line implementation
2019-04-24 fixed merging issues
2019-04-24 manually merged spi implementation
2019-04-28 added tracking of goal
    -improved CPU usage
    -added calibration slider for top border
2019-05-01 pid test
2019-05-01 added missing files
2019-05-01 Revert "added missing files"
    This reverts commit eb39b837ef62d22ee3524b2c97cd034943750c24.
2019-05-01 implemented basic tactic
2019-05-07 updates while RCGO 2019
2019-05-11 addet testpoints to video output file
2019-05-11 optimized cpu usage
    -moved video output from camera to com task
2019-05-12 fixed spi bug and iniparser
2019-05-17 10.05.2019
2019-05-17 cleared up code
2019-05-23 ball, testpoints
    - added "proportion border" for ball
    - scaled down testpoints
2019-05-23 video output
    -lines disappearing when ball/goal not found
    -testpoints changing color
2019-05-25 fixed errors
2019-05-31 Revert "fixed errors"
    This reverts commit 3a258be41d8e0187cd49f8e543c589d767285d84.
2019-05-31 Revert "fixed errors"
    This reverts commit ddd70d97fd3a23ea12741b95b2b67164742842c0.
2019-05-31 Revert "video output"
    This reverts commit fff5ce051f67946f785f55713018a54a8c4c335d.
2019-05-31 Revert "ball, testpoints"
    This reverts commit 9a0610397dabd5915e43279f24d0a7ae7676deb7.
2019-06-01 Testpoints, ballproportion at border
    -colorchanging testpoints
    -lines disappear when not seen
    -change ball proportion at border
2019-06-01 Added Bluetooth ( commented out )
2019-06-01 addet secound testrow
2019-06-01 added mutex (for camera - goal/ball flags))
2019-06-07 fixed mutex errors
2019-06-07 deleted bluetooth
2019-06-07 commented mutex
2019-06-11 good working match
2019-06-16 wip (added distance sensor)
2019-06-20 pre_hannover_final
2019-06-21 fixed crashing match
2019-06-22 while Hannover save
2019-06-24 after hnnover
2019-08-22 basic motor control completed
2019-09-01 usart send working; read to be implemented
2019-09-01 added ability to de-/activate lcd and compass
2019-09-03 transmit working
2019-09-15 non major
2019-09-15 activated lcd and compass in programm
2019-11-24 added noOS wallpaper
2019-11-24 updated wallpapers
2020-02-23 Implementation of BNO055
2020-02-23 receiving data
2020-02-24 BT RC test
2020-02-26 bidirectional data link between robots
2020-02-29 code cleanup
2020-03-05 added support for back mirror
2020-03-06 Kicker implementation working
2020-03-06 wip pre Vöhringen
2020-03-06 wip pre Vöhringen 2
2020-03-06 pre Vöhringen final
2020-03-07 while Vöhringen good working
2020-03-11 basic implementation
2020-03-23 basic serial communication working
2020-03-28 further implementation of serial ui
2020-03-29 bricked version...
2020-04-04 new start with serial as base
2020-04-05 save before including BNO055
2020-04-05 BNO055 implementation complete
2020-04-05 very good turning to origin
    works with noOS SUI 0.4.2
    robot returns quickly to origin with very little overshoot
    tested with pololu 20.4:1 MP gearmotor
2020-06-21 Uploaded Mirror Simulation Files
2020-06-21 Added Blender Files (Trailer)
